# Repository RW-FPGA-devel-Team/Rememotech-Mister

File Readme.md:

# Rememotech MTX port for MiSTer FPGA Board.

Originbal development from Andy.Z.Key : http://www.nyangau.org/rememotech/rememotech.htm

REMEMOTECH is a modern-day re-implementation of a Memotech MTX/FDX/SDX compatible computer :-

    in VHDL
    re-using existing VHDL definitions of major chips
    writing VHDL definitions of missing chips
    writing the glue logic in VHDL
    synthesizing for a Cyclone II FPGA and targetting an Altera DE1 board
    exploiting the hardware on the board, around the FPGA, such as clock, connectors, 
    Flash, SRAM, VGA DACs, sound CODEC, SD Card, ... 

It implements enough hardware to allow it to run MTX BASIC, various MTX games and CP/M. It supports :-

    Z80 compatible CPU, at 4.166MHz and other speeds upto 25MHz
    384KB RAM, 72KB ROM
    PS/2 keyboard
    VDP, outputting to 640x480 @ 50Hz (or 60Hz) VGA
    Sound chip
    80 column card support, with 80x24 and 80x48 modes, outputting to 640x480 @ 60Hz VGA
    Whether VDP or 80 column output appears on main VGA output switchable
    The other display can appear on another VGA, via a daughter card
    RAM Disc support (upto 320KB)
    SD Card as a large and fast alternative to floppy disk
    Modified SDX ROM using SD Card and RAM Disc instead of floppy disk
    Virtual cassette support
    Numeric accelerator

For the port to MiSTer, video has been re-implemented in VGA and HDMI and access to the storage is done through a VHD file.
Each VHD file can have upto 8 8MB partitions. (64 MB Max) Each of these would contain a CP/M 2.2 filesystem. 

The Flash image is embedded into the core, and contains a raw 512KB image of the Flash (which contains ROM images and the initial RAM Disc image). 

You'll need to use RECONFIG.COM to configure a drive (or drives) to access partitions on the SD Card. Type codes 18..1F correspond to 8MB partitions 0 to 7 on the card. eg: To access partitions 0, 1 and 2 :-

A>RECONFIG B:18,C:19,D:1A

    You can switch to MTX BASIC, and use ROM 5 to gain access to disk via USER commands.
    
    A>MTXL
    ROM 5
    USER DIR
    USER RUN "SOFT.RUN"

For the TAPES, use RETAPE

    You can switch to MTX BASIC, and use ROM 5 to gain access to disk via USER commands.
    
    RETAPE "TAPE.MTX"
    MTXL
    LOAD "TAPE"

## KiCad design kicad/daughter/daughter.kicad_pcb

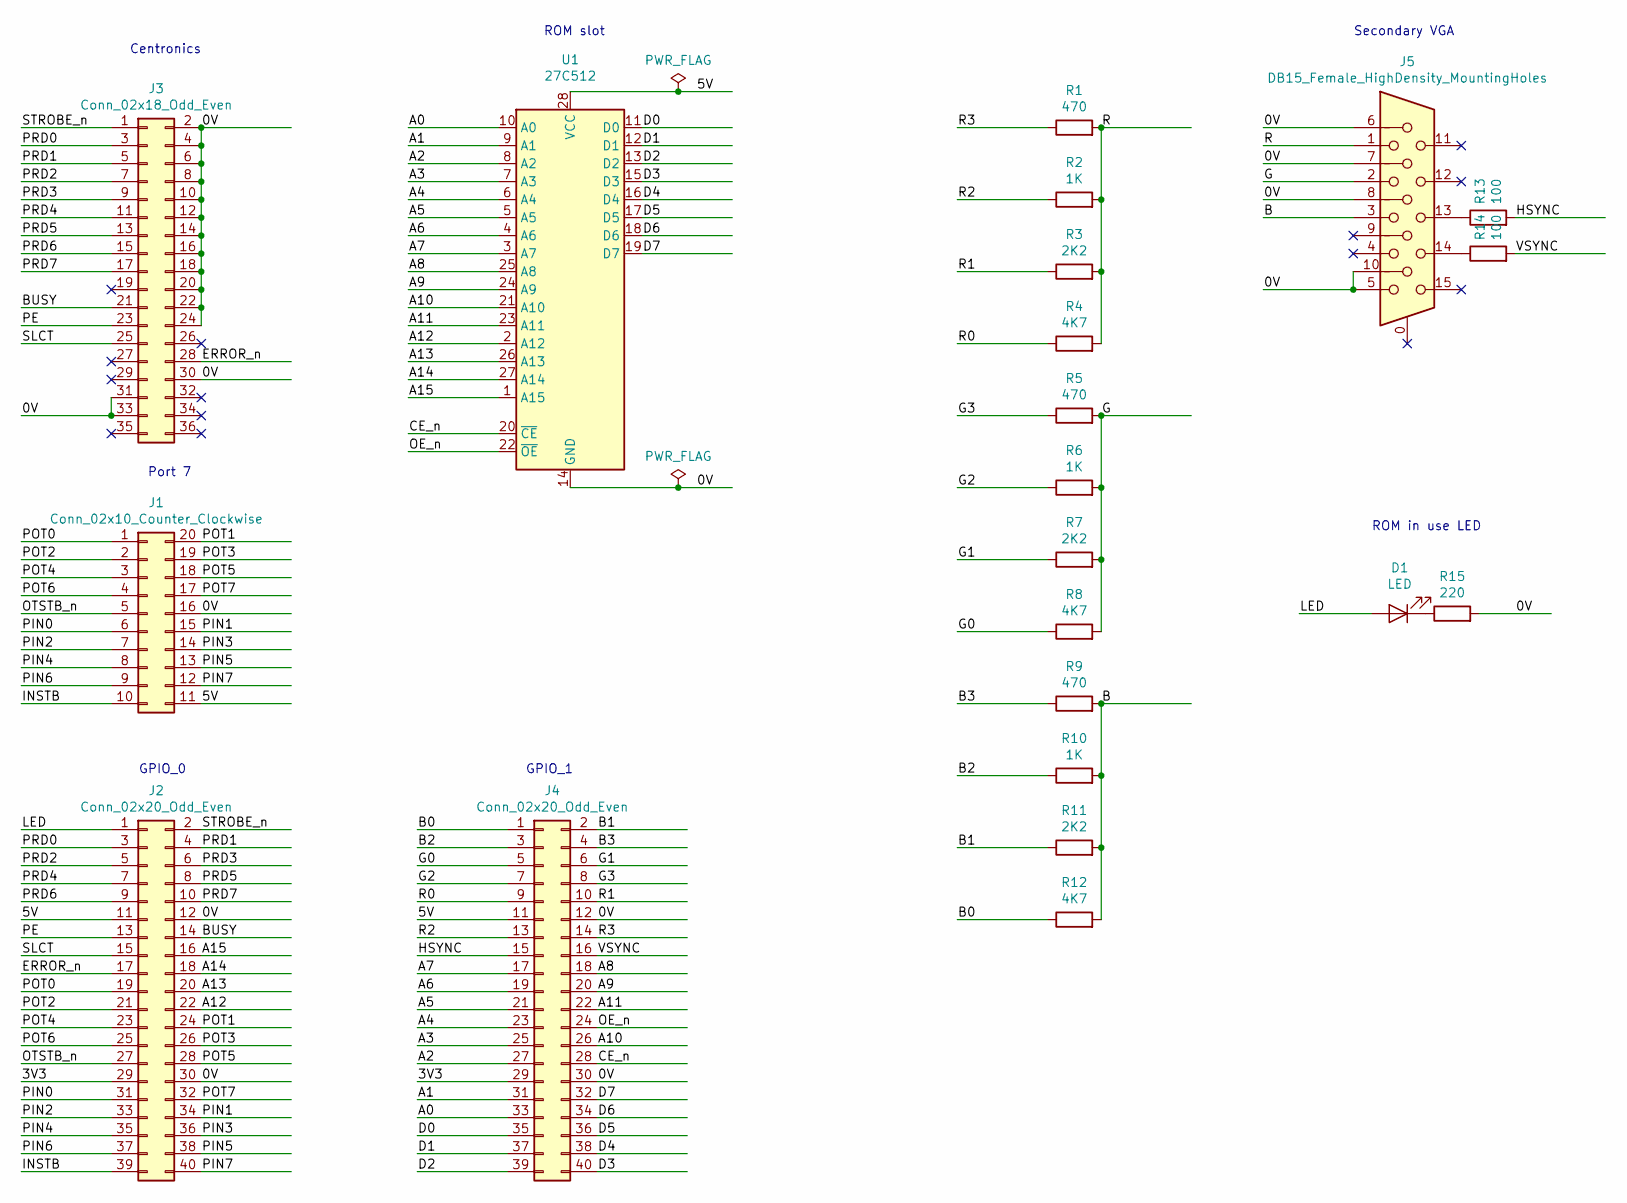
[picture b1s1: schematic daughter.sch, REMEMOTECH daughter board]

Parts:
D1: LED; LED_D4.0mm
J1: Conn_02x10_Counter_Clockwise; DIP-20_W7.62mm_Socket
J2, J4: Conn_02x20_Odd_Even; PinHeader_2x20_P2.54mm_Vertical
J3: Conn_02x18_Odd_Even; PinHeader_2x18_P2.54mm_Vertical
J5: DB15_Female_HighDensity_MountingHoles; DSUB-15-HD_Female_Horizontal_P2.29x1.98mm_EdgePinOffset3.03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
R1, R5, R9: 470; R_Axial_DIN0207_L6.3mm_D2.5mm_P7.62mm_Horizontal
R2, R6, R10: 1K; R_Axial_DIN0207_L6.3mm_D2.5mm_P7.62mm_Horizontal
R3, R7, R11: 2K2; R_Axial_DIN0207_L6.3mm_D2.5mm_P7.62mm_Horizontal
R4, R8, R12: 4K7; R_Axial_DIN0207_L6.3mm_D2.5mm_P7.62mm_Horizontal
R13, R14: 100; R_Axial_DIN0207_L6.3mm_D2.5mm_P7.62mm_Horizontal
R15: 220; R_Axial_DIN0207_L6.3mm_D2.5mm_P7.62mm_Horizontal
U1: 27C512; DIP-28_W15.24mm_Socket

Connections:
/0V: J1.16, J2.12, J2.30, J3.2, J3.4, J3.6, J3.8, J3.10, J3.12, J3.14, J3.16, J3.18, J3.20, J3.22, J3.24, J3.30, J3.31, J3.33, J4.12, J4.30, J5.5, J5.6, J5.7, J5.8, J5.10, R15.2, U1.14 (GND)
/3V3: J2.29, J4.29
/5V: J1.11, J2.11, J4.11, U1.28 (VCC)
/A0: J4.33, U1.10 (A0)
/A1: J4.31, U1.9 (A1)
/A2: J4.27, U1.8 (A2)
/A3: J4.25, U1.7 (A3)
/A4: J4.23, U1.6 (A4)
/A5: J4.21, U1.5 (A5)
/A6: J4.19, U1.4 (A6)
/A7: J4.17, U1.3 (A7)
/A8: J4.18, U1.25 (A8)
/A9: J4.20, U1.24 (A9)
/A10: J4.26, U1.21 (A10)
/A11: J4.22, U1.23 (A11)
/A12: J2.22, U1.2 (A12)
/A13: J2.20, U1.26 (A13)
/A14: J2.18, U1.27 (A14)
/A15: J2.16, U1.1 (A15)
/B: J5.3, R9.2, R10.2, R11.2, R12.2
/B0: J4.1, R12.1
/B1: J4.2, R11.1
/B2: J4.3, R10.1
/B3: J4.4, R9.1
/BUSY: J2.14, J3.21
/CE_n: J4.28, U1.20 (~CE)
/D0: J4.35, U1.11 (D0)
/D1: J4.37, U1.12 (D1)
/D2: J4.39, U1.13 (D2)
/D3: J4.40, U1.15 (D3)
/D4: J4.38, U1.16 (D4)
/D5: J4.36, U1.17 (D5)
/D6: J4.34, U1.18 (D6)
/D7: J4.32, U1.19 (D7)
/ERROR_n: J2.17, J3.28
/G: J5.2, R5.2, R6.2, R7.2, R8.2
/G0: J4.5, R8.1
/G1: J4.6, R7.1
/G2: J4.7, R6.1
/G3: J4.8, R5.1
/HSYNC: J4.15, R13.2
/INSTB: J1.10, J2.39
/LED: D1.2 (A), J2.1
/OE_n: J4.24, U1.22 (~OE)
/OTSTB_n: J1.5, J2.27
/PE: J2.13, J3.23
/PIN0: J1.6, J2.31
/PIN1: J1.15, J2.34
/PIN2: J1.7, J2.33
/PIN3: J1.14, J2.36
/PIN4: J1.8, J2.35
/PIN5: J1.13, J2.38
/PIN6: J1.9, J2.37
/PIN7: J1.12, J2.40
/POT0: J1.1, J2.19
/POT1: J1.20, J2.24
/POT2: J1.2, J2.21
/POT3: J1.19, J2.26
/POT4: J1.3, J2.23
/POT5: J1.18, J2.28
/POT6: J1.4, J2.25
/POT7: J1.17, J2.32
/PRD0: J2.3, J3.3
/PRD1: J2.4, J3.5
/PRD2: J2.5, J3.7
/PRD3: J2.6, J3.9
/PRD4: J2.7, J3.11
/PRD5: J2.8, J3.13
/PRD6: J2.9, J3.15
/PRD7: J2.10, J3.17
/R: J5.1, R1.2, R2.2, R3.2, R4.2
/R0: J4.9, R4.1
/R1: J4.10, R3.1
/R2: J4.13, R2.1
/R3: J4.14, R1.1
/SLCT: J2.15, J3.25
/STROBE_n: J2.2, J3.1
/VSYNC: J4.16, R14.2
unnamed: D1.1 (K), R15.1
unnamed: J5.13, R13.1
unnamed: J5.14, R14.1

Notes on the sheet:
Centronics
ROM slot
Secondary VGA
Port 7
GPIO_0
GPIO_1
ROM in use LED

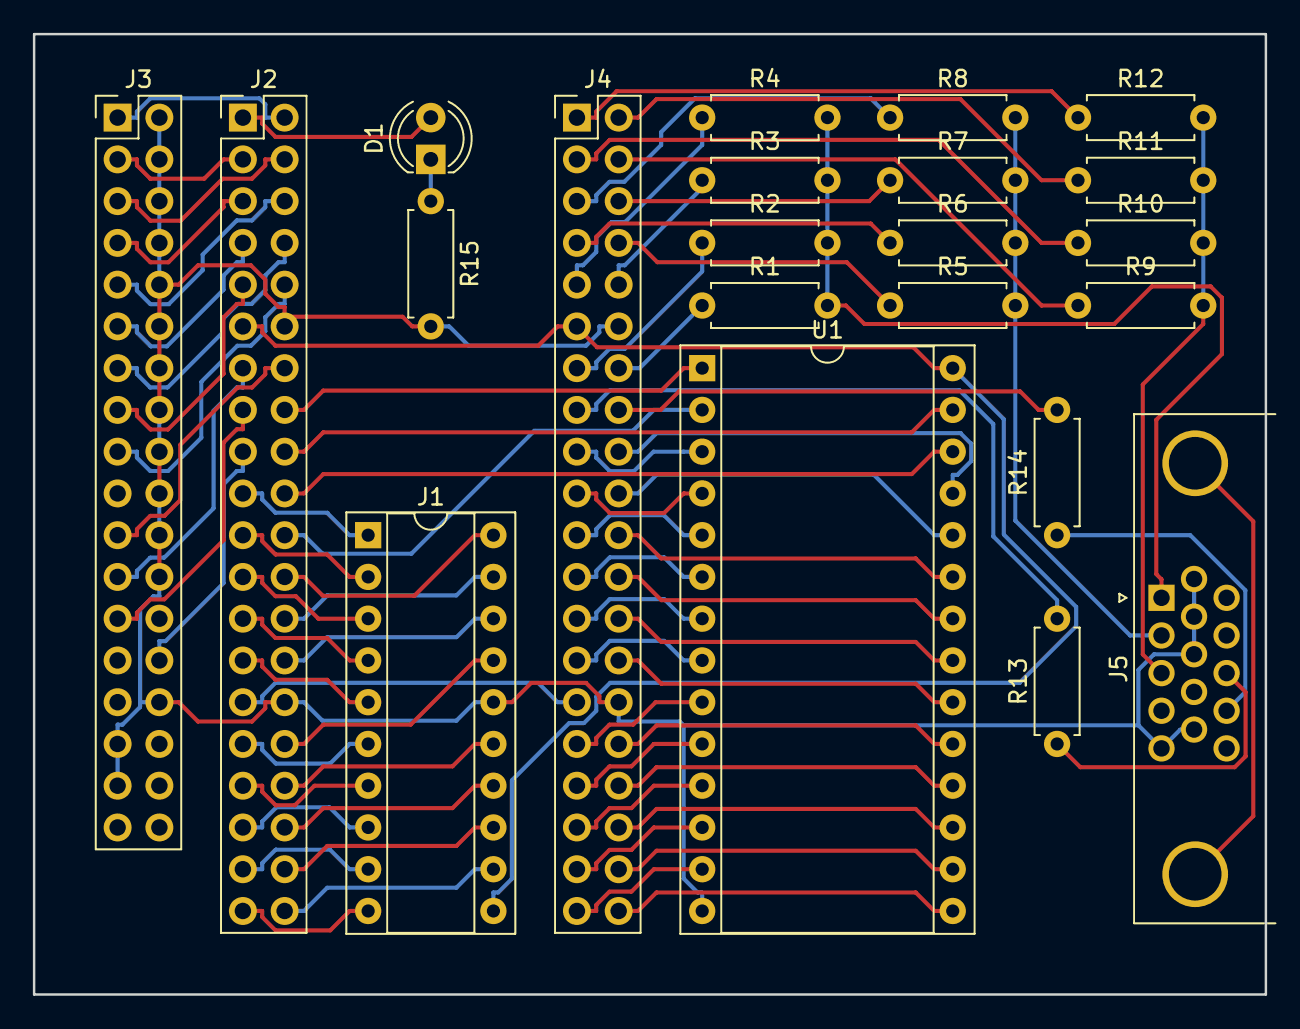
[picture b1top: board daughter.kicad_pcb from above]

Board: 2 copper layers, 74.9 x 58.4 mm, 22 parts (0 on the bottom side), 81 nets.

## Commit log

2020-05-28 log erased
2020-05-28 diskdefs for memotech filesystem
2020-05-29 SD in progress
2020-05-30 Alpha Version
    Includes :
2020-05-30 Change Video Signal "Expansion"
2020-05-30 garbage cleaning....
2020-06-01 Wip Lectura VHDL
2020-06-01 VHD disks working
2020-06-02 Solved VHD. Thanks to Rampa69.
2020-06-02 VHD Fixes Part 2 :)
